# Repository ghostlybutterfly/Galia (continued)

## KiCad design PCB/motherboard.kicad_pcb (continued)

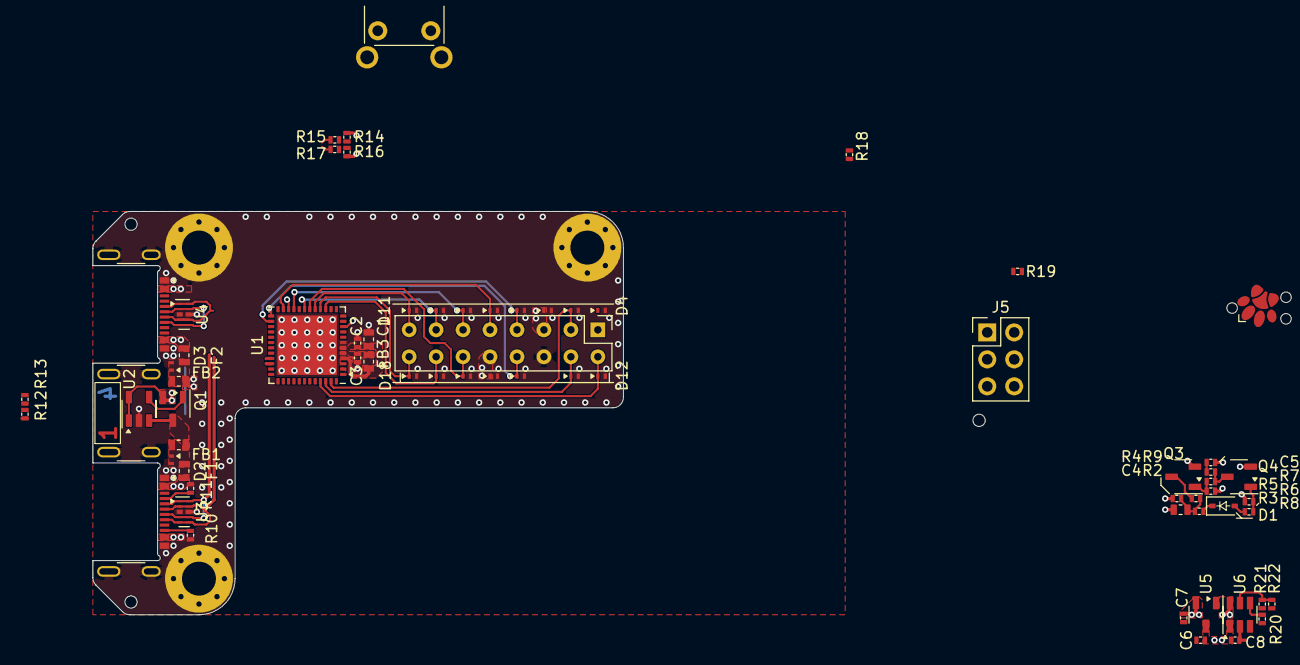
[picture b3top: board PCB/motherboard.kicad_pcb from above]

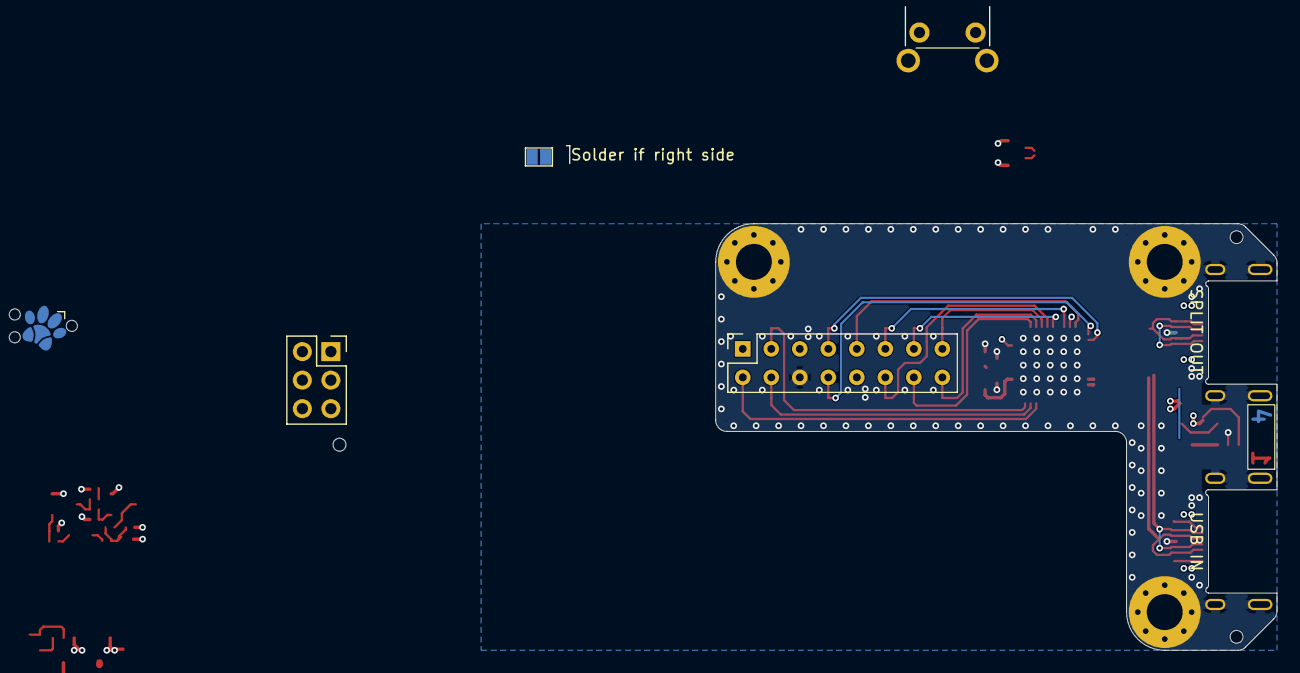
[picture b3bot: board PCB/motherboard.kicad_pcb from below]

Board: 4 copper layers, 50.0 x 38.0 mm, 74 parts (4 on the bottom side), 45 nets.
